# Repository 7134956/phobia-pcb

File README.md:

This repository contains schematic and printed circuit board design files.
There is KiCad project. Refer to the PMC repository for details.

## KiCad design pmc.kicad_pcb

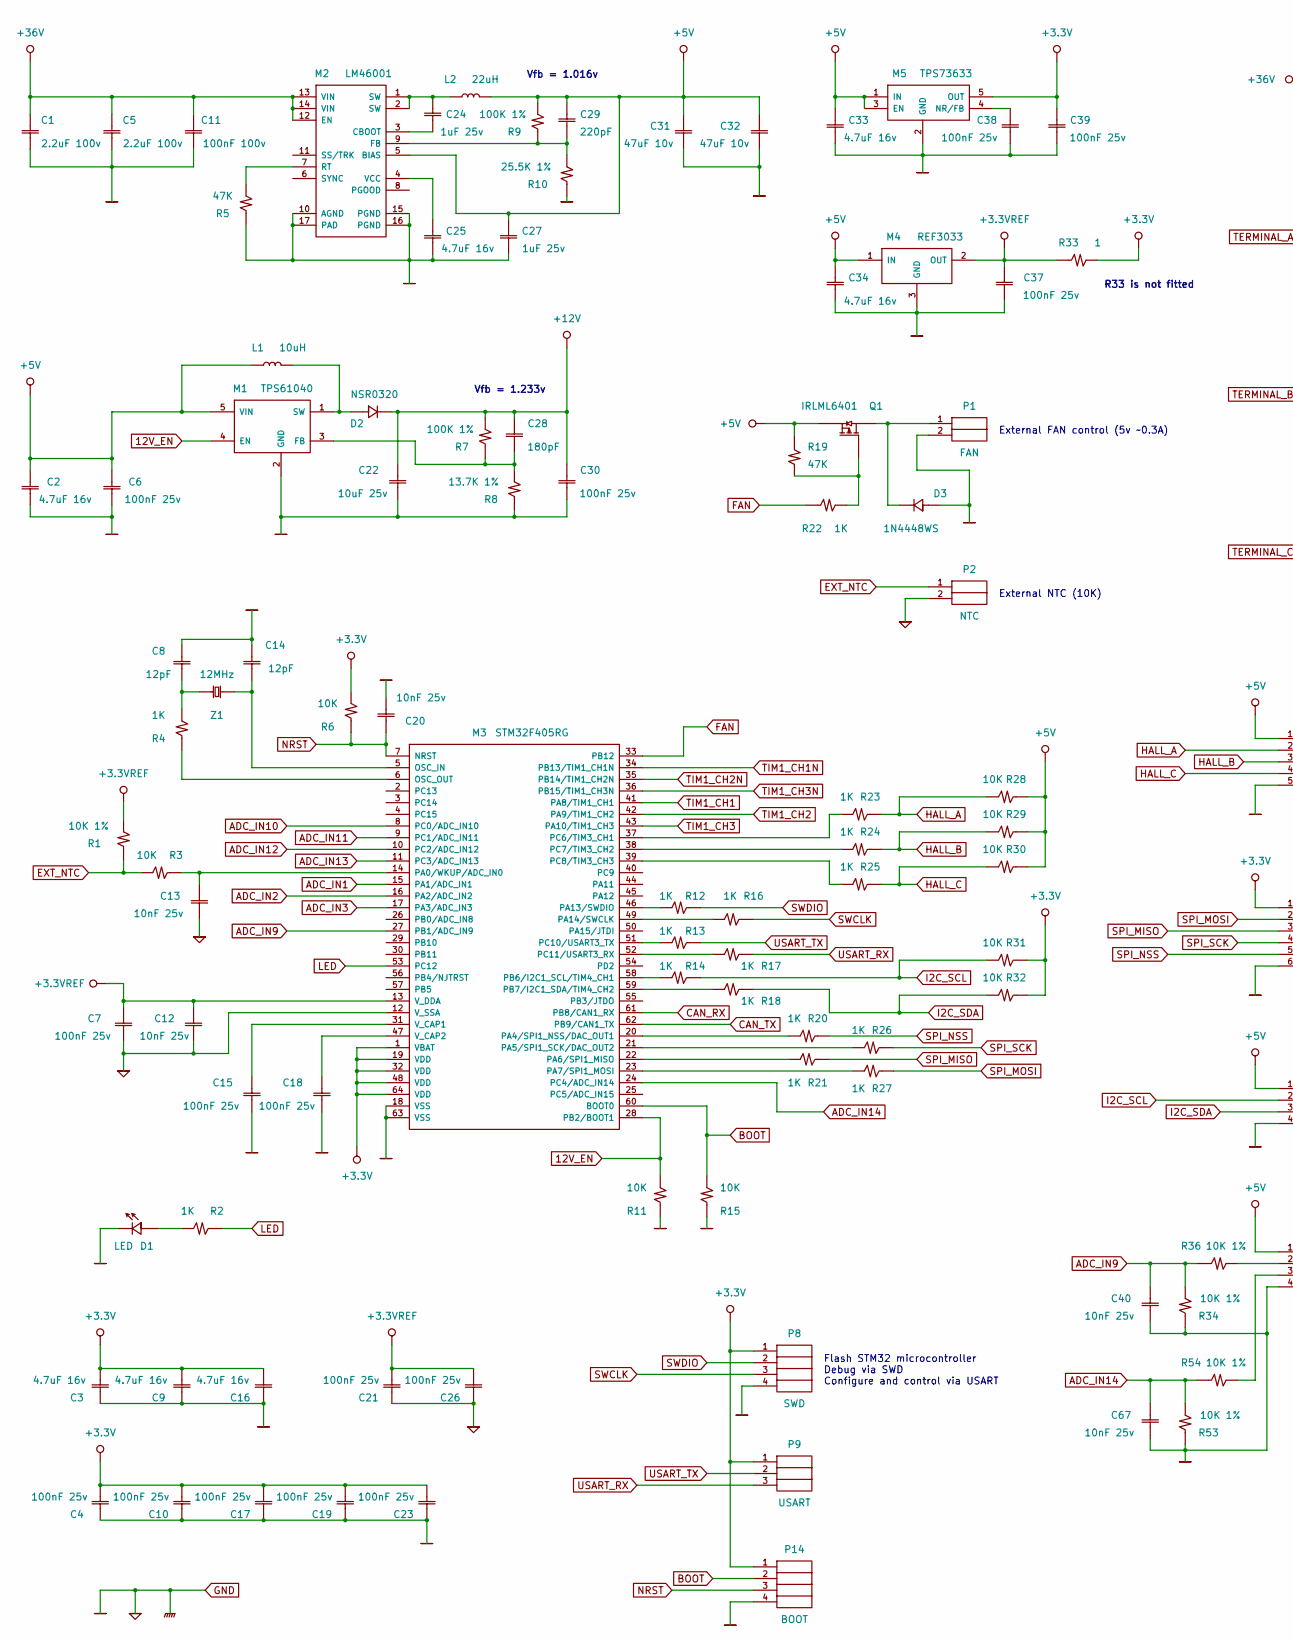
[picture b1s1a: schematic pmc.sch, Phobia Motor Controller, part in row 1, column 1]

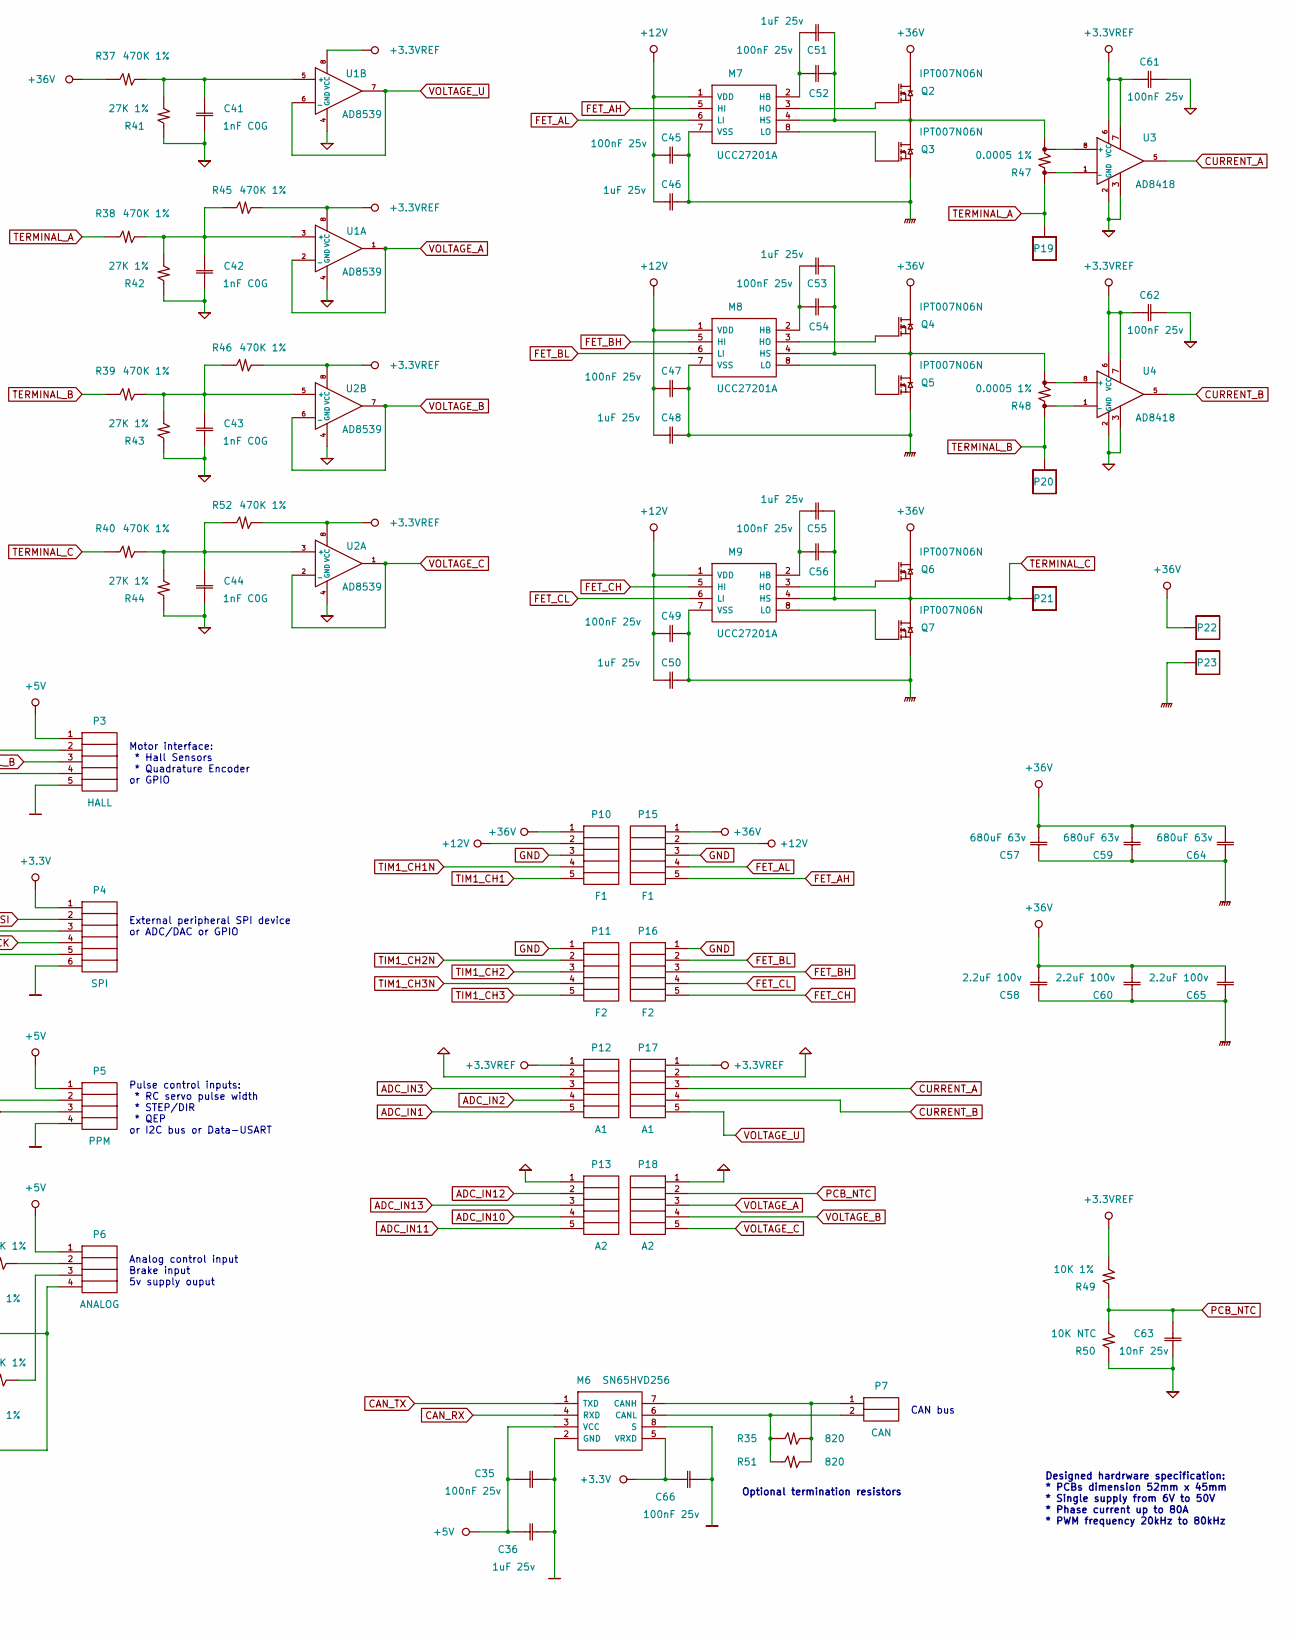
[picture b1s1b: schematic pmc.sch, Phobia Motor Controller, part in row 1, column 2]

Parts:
C1, C5, C58, C60, C65: 2.2uF 100v; SM-1210
C2, C3, C9, C16, C25, C33, C34: 4.7uF 16v; SM-0805
C4, C6, C7, C10, C15, C17, C18, C19, C21, C23, C26, C30, C35, C37, C38, C39, C45, C47, C49, C52, C54, C56, C61, C62, C66: 100nF 25v; SM-0603
C8, C14: 12pF; SM-0603
C11: 100nF 100v; SM-0805
C12, C13, C20, C40, C63, C67: 10nF 25v; SM-0603
C22: 10uF 25v; SM-1210
C24, C27, C36, C46, C48, C50, C51, C53, C55: 1uF 25v; SM-0805
C28: 180pF; SM-0603
C29: 220pF; SM-0603
C31, C32: 47uF 10v; SM-1210
C41, C42, C43, C44: 1nF C0G; SM-0603
C57, C59, C64: 680uF 63v; CE135-E
D1: LED; SM-0603
D2: NSR0320; SM-0805
D3: 1N4448WS; SM-0805
L1: 10uH; COIL-3
L2: 22uH; COIL-8
M1: TPS61040; SOT-23-5
M2: LM46001; HTSSOP-16
M3: STM32F405RG; LQFP-64
M4: REF3033; SOT-23
M5: TPS73633; SOT-23-5
M6: SN65HVD256; SO-8
M7, M8, M9: UCC27201A; SON-8
P1: FAN; PLS-2
P2: NTC; PLS-2
P3: HALL; PLS-5
P4: SPI; PLS-6
P5: PPM; PLS-4
P6: ANALOG; PLS-4
P7: CAN; PLS-2
P8: SWD; PLS-4
P9: USART; PLS-3
P10, P15: F1; PLS-5
P11, P16: F2; PLS-5
P12, P17: A1; PLS-5
P13, P18: A2; PLS-5
P14: BOOT; PLS-4
P19, P20, P21, P22, P23: CONN4; PAD-1
Q1: IRLML6401; SOT-23
Q2, Q3, Q4, Q5, Q6, Q7: IPT007N06N; PG-HSOF-8
R1, R34, R36, R49, R53, R54: 10K 1%; SM-0603
R2, R4, R12, R13, R14, R16, R17, R18, R20, R21, R22, R23, R24, R25, R26, R27: 1K; SM-0603
R3, R6, R11, R15, R28, R29, R30, R31, R32: 10K; SM-0603
R5, R19: 47K; SM-0603
R7, R9: 100K 1%; SM-0603
R8: 13.7K 1%; SM-0603
R10: 25.5K 1%; SM-0603
R33: 1; SM-0603
R35, R51: 820; SM-1206
R37, R38, R39, R40, R45, R46, R52: 470K 1%; SM-0603
R41, R42, R43, R44: 27K 1%; SM-0603
R47, R48: 0.0005 1%; LR2512-4
R50: 10K NTC; SM-0805
U1, U2: AD8539; MSOP-8
U3, U4: AD8418; MSOP-8
Z1: 12MHz; SM-Z3225

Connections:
12V_EN: M1.4 (EN), M3.28 (PB2/BOOT1), R11.2
+3.3V: C3.1, C4.1, C9.1, C10.1, C16.1, C17.1, C19.1, C23.1, C39.1, C66.1, M3.1 (VBAT), M3.19 (VDD), M3.32 (VDD), M3.48 (VDD), M3.64 (VDD), M5.5 (OUT), M6.5 (VRXD), P4.1, P8.1, P9.1, P14.1, R6.2, R31.1, R32.1, R33.2
+3.3VREF: C7.1, C12.1, C21.1, C26.1, C37.1, C61.2, C62.2, M3.13 (V_DDA), M4.2 (OUT), P12.1, P17.1, R1.2, R33.1, R45.2, R46.2, R49.2, R52.2, U1.8 (VCC), U2.8 (VCC), U3.6 (VCC), U3.7, U4.6 (VCC), U4.7
+5V: C2.1, C6.1, C27.1, C29.1, C31.1, C32.1, C33.1, C34.1, C35.2, C36.2, L1.1, L2.2, M1.5 (VIN), M2.5 (BIAS), M4.1 (IN), M5.1 (IN), M5.3 (EN), M6.3 (VCC), P3.1, P5.1, P6.1, Q1.2 (S), R9.2, R19.1, R28.1, R29.1, R30.1
+12V: C22.1, C28.1, C30.1, C45.2, C46.1, C47.2, C48.2, C49.2, C50.2, D2.1, M7.1 (VDD), M8.1 (VDD), M9.1 (VDD), P10.2, P15.2, R7.2
+36V: C1.2, C5.2, C11.2, C57.1, C58.1, C59.1, C60.1, C64.1, C65.1, M2.12 (EN), M2.13 (VIN), M2.14 (VIN), P10.1, P15.1, P22.1, Q2.3 (D), Q4.3 (D), Q6.3 (D), R37.1
ADC_IN1: M3.15 (PA1/ADC_IN1), P12.5
ADC_IN2: M3.16 (PA2/ADC_IN2), P12.4
ADC_IN3: M3.17 (PA3/ADC_IN3), P12.3
ADC_IN9: C40.2, M3.27 (PB1/ADC_IN9), R34.2, R36.1
ADC_IN10: M3.8 (PC0/ADC_IN10), P13.4
ADC_IN11: M3.9 (PC1/ADC_IN11), P13.5
ADC_IN12: M3.10 (PC2/ADC_IN12), P13.2
ADC_IN13: M3.11 (PC3/ADC_IN13), P13.3
ADC_IN14: C67.2, M3.24 (PC4/ADC_IN14), R53.2, R54.1
BOOT: M3.60 (BOOT0), P14.2, R15.2
CAN_RX: M3.61 (PB8/CAN1_RX), M6.4 (RXD)
CAN_TX: M3.62 (PB9/CAN1_TX), M6.1 (TXD)
CURRENT_A: P17.3, U3.5
CURRENT_B: P17.4, U4.5
EXT_NTC: P2.1, R1.1, R3.2
FAN: M3.33 (PB12), R22.1
FET_AH: M7.5 (HI), P15.5
FET_AL: M7.6 (LI), P15.4
FET_BH: M8.5 (HI), P16.3
FET_BL: M8.6 (LI), P16.2
FET_CH: M9.5 (HI), P16.5
FET_CL: M9.6 (LI), P16.4
GND: C1.1, C2.2, C3.2, C4.2, C5.1, C6.2, C7.2, C8.1, C9.2, C10.2, C11.1, C12.2, C13.1, C14.1, C15.2, C16.2, C17.2, C18.2, C19.2, C20.1, C21.2, C22.2, C23.2, C25.2, C26.2, C27.2, C30.2, C31.2, C32.2, C33.2, C34.2, C35.1, C36.1, C37.2, C38.2, C39.2, C40.1, C41.2, C42.2, C43.2, C44.2, C45.1, C46.2, C47.1, C48.1, C49.1, C50.1, C57.2, C58.2, C59.2, C60.2, C61.1, C62.1, C63.1, C64.2, C65.2, C66.2, C67.1, D1.1, D3.2, M1.2 (GND), M2.10 (AGND), M2.15 (PGND), M2.16 (PGND), M2.17 (PAD), M3.12 (V_SSA), M3.18 (VSS), M3.63 (VSS), M4.3 (GND), M5.2 (GND), M6.2 (GND), M6.8 (S), M7.7 (VSS), M8.7 (VSS), M9.7 (VSS), P1.2, P2.2, P3.5, P4.6, P5.4, P6.4, P8.4, P10.3, P11.1, P12.2, P13.1, P14.4, P15.3, P16.1, P17.2, P18.1, P23.1, Q3.2 (S), Q5.2 (S), Q7.2 (S), R5.1, R8.1, R10.1, R11.1, R15.1, R34.1, R41.1, R42.1, R43.1, R44.1, R50.1, R53.1, U1.4 (GND), U2.4 (GND), U3.2 (GND), U3.3, U4.2 (GND), U4.3; also elsewhere on the board
HALL_A: P3.2, R23.1, R28.2
HALL_B: P3.3, R24.1, R29.2
HALL_C: P3.4, R25.1, R30.2
I2C_SCL: P5.2, R14.1, R31.2
I2C_SDA: P5.3, R18.1, R32.2
LED: M3.53 (PC12), R2.1
NC: U3.4 (NC), U4.4 (NC)
NRST: C20.2, M3.7 (NRST), P14.3, R6.1
unnamed: C8.2, R4.2, Z1.1
unnamed: C13.2, M3.14 (PA0/WKUP/ADC_IN0), R3.1
unnamed: C14.2, M3.5 (OSC_IN), Z1.2
unnamed: C15.1, M3.31 (V_CAP1)
unnamed: C18.1, M3.47 (V_CAP2)
unnamed: C24.1, L2.1, M2.1 (SW), M2.2 (SW)
unnamed: C24.2, M2.3 (CBOOT)
unnamed: C25.1, M2.4 (VCC)
unnamed: C28.2, M1.3 (FB), R7.1, R8.2
unnamed: C29.2, M2.9 (FB), R9.1, R10.2
unnamed: C38.1, M5.4 (NR/FB)
unnamed: C41.1, R37.2, R41.2, U1.5 (+)
unnamed: C42.1, R38.2, R42.2, R45.1, U1.3 (+)
unnamed: C43.1, R39.2, R43.2, R46.1, U2.5 (+)
unnamed: C44.1, R40.2, R44.2, R52.1, U2.3 (+)
unnamed: C51.1, C52.1, M7.4 (HS), Q2.2 (S), Q3.3 (D), R47.1
unnamed: C51.2, C52.2, M7.2 (HB)
unnamed: C53.1, C54.1, M8.4 (HS), Q4.2 (S), Q5.3 (D), R48.1
unnamed: C53.2, C54.2, M8.2 (HB)
unnamed: C55.2, C56.2, M9.2 (HB)
unnamed: D1.2, R2.2
unnamed: D2.2, L1.2, M1.1 (SW)
unnamed: D3.1, P1.1, Q1.3 (D)
unnamed: M2.7 (RT), R5.2
unnamed: M3.6 (OSC_OUT), R4.1
unnamed: M3.20 (PA4/SPI1_NSS/DAC_OUT1), R20.2
unnamed: M3.21 (PA5/SPI1_SCK/DAC_OUT2), R26.2
unnamed: M3.22 (PA6/SPI1_MISO), R21.2
unnamed: M3.23 (PA7/SPI1_MOSI), R27.2
unnamed: M3.37 (PC6/TIM3_CH1), R23.2
unnamed: M3.38 (PC7/TIM3_CH2), R24.2
unnamed: M3.39 (PC8/TIM3_CH3), R25.2
unnamed: M3.46 (PA13/SWDIO), R12.2
unnamed: M3.49 (PA14/SWCLK), R16.2
unnamed: M3.51 (PC10/USART3_TX), R13.2
unnamed: M3.52 (PC11/USART3_RX), R17.2
unnamed: M3.58 (PB6/I2C1_SCL/TIM4_CH1), R14.2
unnamed: M3.59 (PB7/I2C1_SDA/TIM4_CH2), R18.2
unnamed: M6.6 (CANL), P7.2, R35.1, R51.1
unnamed: M6.7 (CANH), P7.1, R35.2, R51.2
unnamed: M7.3 (HO), Q2.1 (G)
unnamed: M7.8 (LO), Q3.1 (G)
unnamed: M8.3 (HO), Q4.1 (G)
unnamed: M8.8 (LO), Q5.1 (G)
unnamed: M9.3 (HO), Q6.1 (G)
unnamed: M9.8 (LO), Q7.1 (G)
unnamed: P6.2, R36.2
unnamed: P6.3, R54.2
unnamed: Q1.1 (G), R19.2, R22.2
unnamed: R47.3, U3.8 (+)
unnamed: R47.4, U3.1 (_)
unnamed: R48.3, U4.8 (+)
unnamed: R48.4, U4.1 (_)
PCB_NTC: C63.2, P18.2, R49.1, R50.2
SPI_MISO: P4.3, R21.1
SPI_MOSI: P4.2, R27.1
SPI_NSS: P4.5, R20.1
SPI_SCK: P4.4, R26.1
SWCLK: P8.3, R16.1
SWDIO: P8.2, R12.1
TERMINAL_A: P19.1, R38.1, R47.2
TERMINAL_B: P20.1, R39.1, R48.2
TERMINAL_C: C55.1, C56.1, M9.4 (HS), P21.1, Q6.2 (S), Q7.3 (D), R40.1
TIM1_CH1: M3.41 (PA8/TIM1_CH1), P10.5
TIM1_CH1N: M3.34 (PB13/TIM1_CH1N), P10.4
TIM1_CH2: M3.42 (PA9/TIM1_CH2), P11.3
TIM1_CH2N: M3.35 (PB14/TIM1_CH2N), P11.2
TIM1_CH3: M3.43 (PA10/TIM1_CH3), P11.5
TIM1_CH3N: M3.36 (PB15/TIM1_CH3N), P11.4
USART_RX: P9.3, R17.1
USART_TX: P9.2, R13.1
VOLTAGE_A: P18.3, U1.1, U1.2 (_)
VOLTAGE_B: P18.4, U2.6 (_), U2.7
VOLTAGE_C: P18.5, U2.1, U2.2 (_)
VOLTAGE_U: P17.5, U1.6 (_), U1.7

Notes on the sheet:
Motor interface: * Hall Sensors * Quadrature Encoder or GPIO
External peripheral SPI device or ADC/DAC or GPIO
Pulse control inputs: * RC servo pulse width * STEP/DIR * QEP or I2C bus or Data-USART
Flash STM32 microcontroller Debug via SWD Configure and control via USART
Designed hardrware specification: * PCBs dimension 52mm x 45mm * Single supply from 6V to 50V * Phase current up to 80A * PWM frequency 20kHz to 80kHz
Optional termination resistors
Analog control input Brake input 5v supply ouput
External NTC (10K)
External FAN control (5v ~~0.3A)
CAN bus
R33 is not fitted
Vfb = 1.016v
Vfb = 1.233v

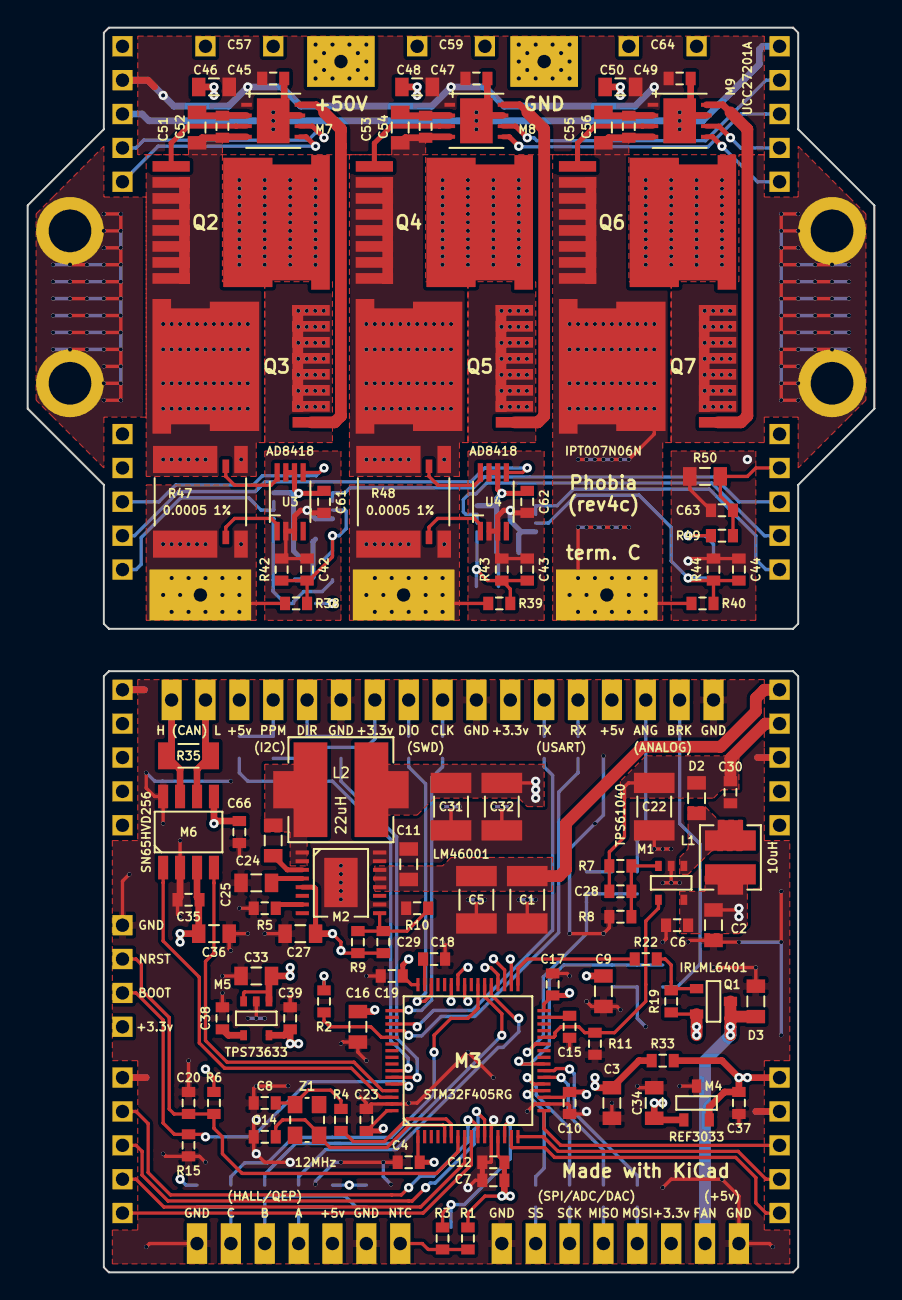
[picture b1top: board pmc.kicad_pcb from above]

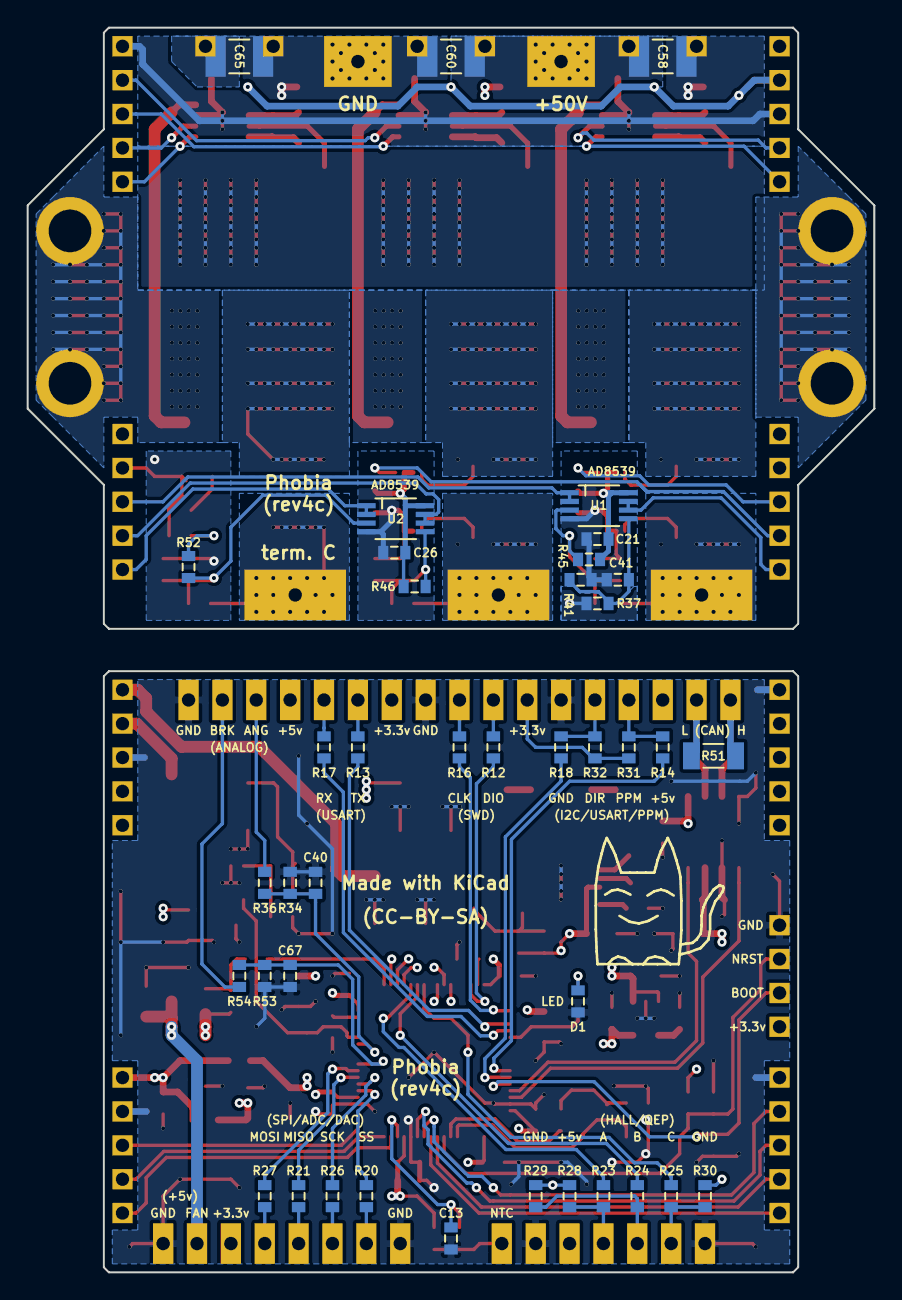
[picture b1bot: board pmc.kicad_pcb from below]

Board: 8 copper layers, 63.5 x 93.3 mm, 174 parts (40 on the bottom side), 112 nets.

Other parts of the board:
PLS-1, PLS-1#2, PLS-1#3, PLS-1#4: VAL**; PLS-1

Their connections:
GND: PLS-1.1, PLS-1#2.1, PLS-1#3.1, PLS-1#4.1; also elsewhere on the board

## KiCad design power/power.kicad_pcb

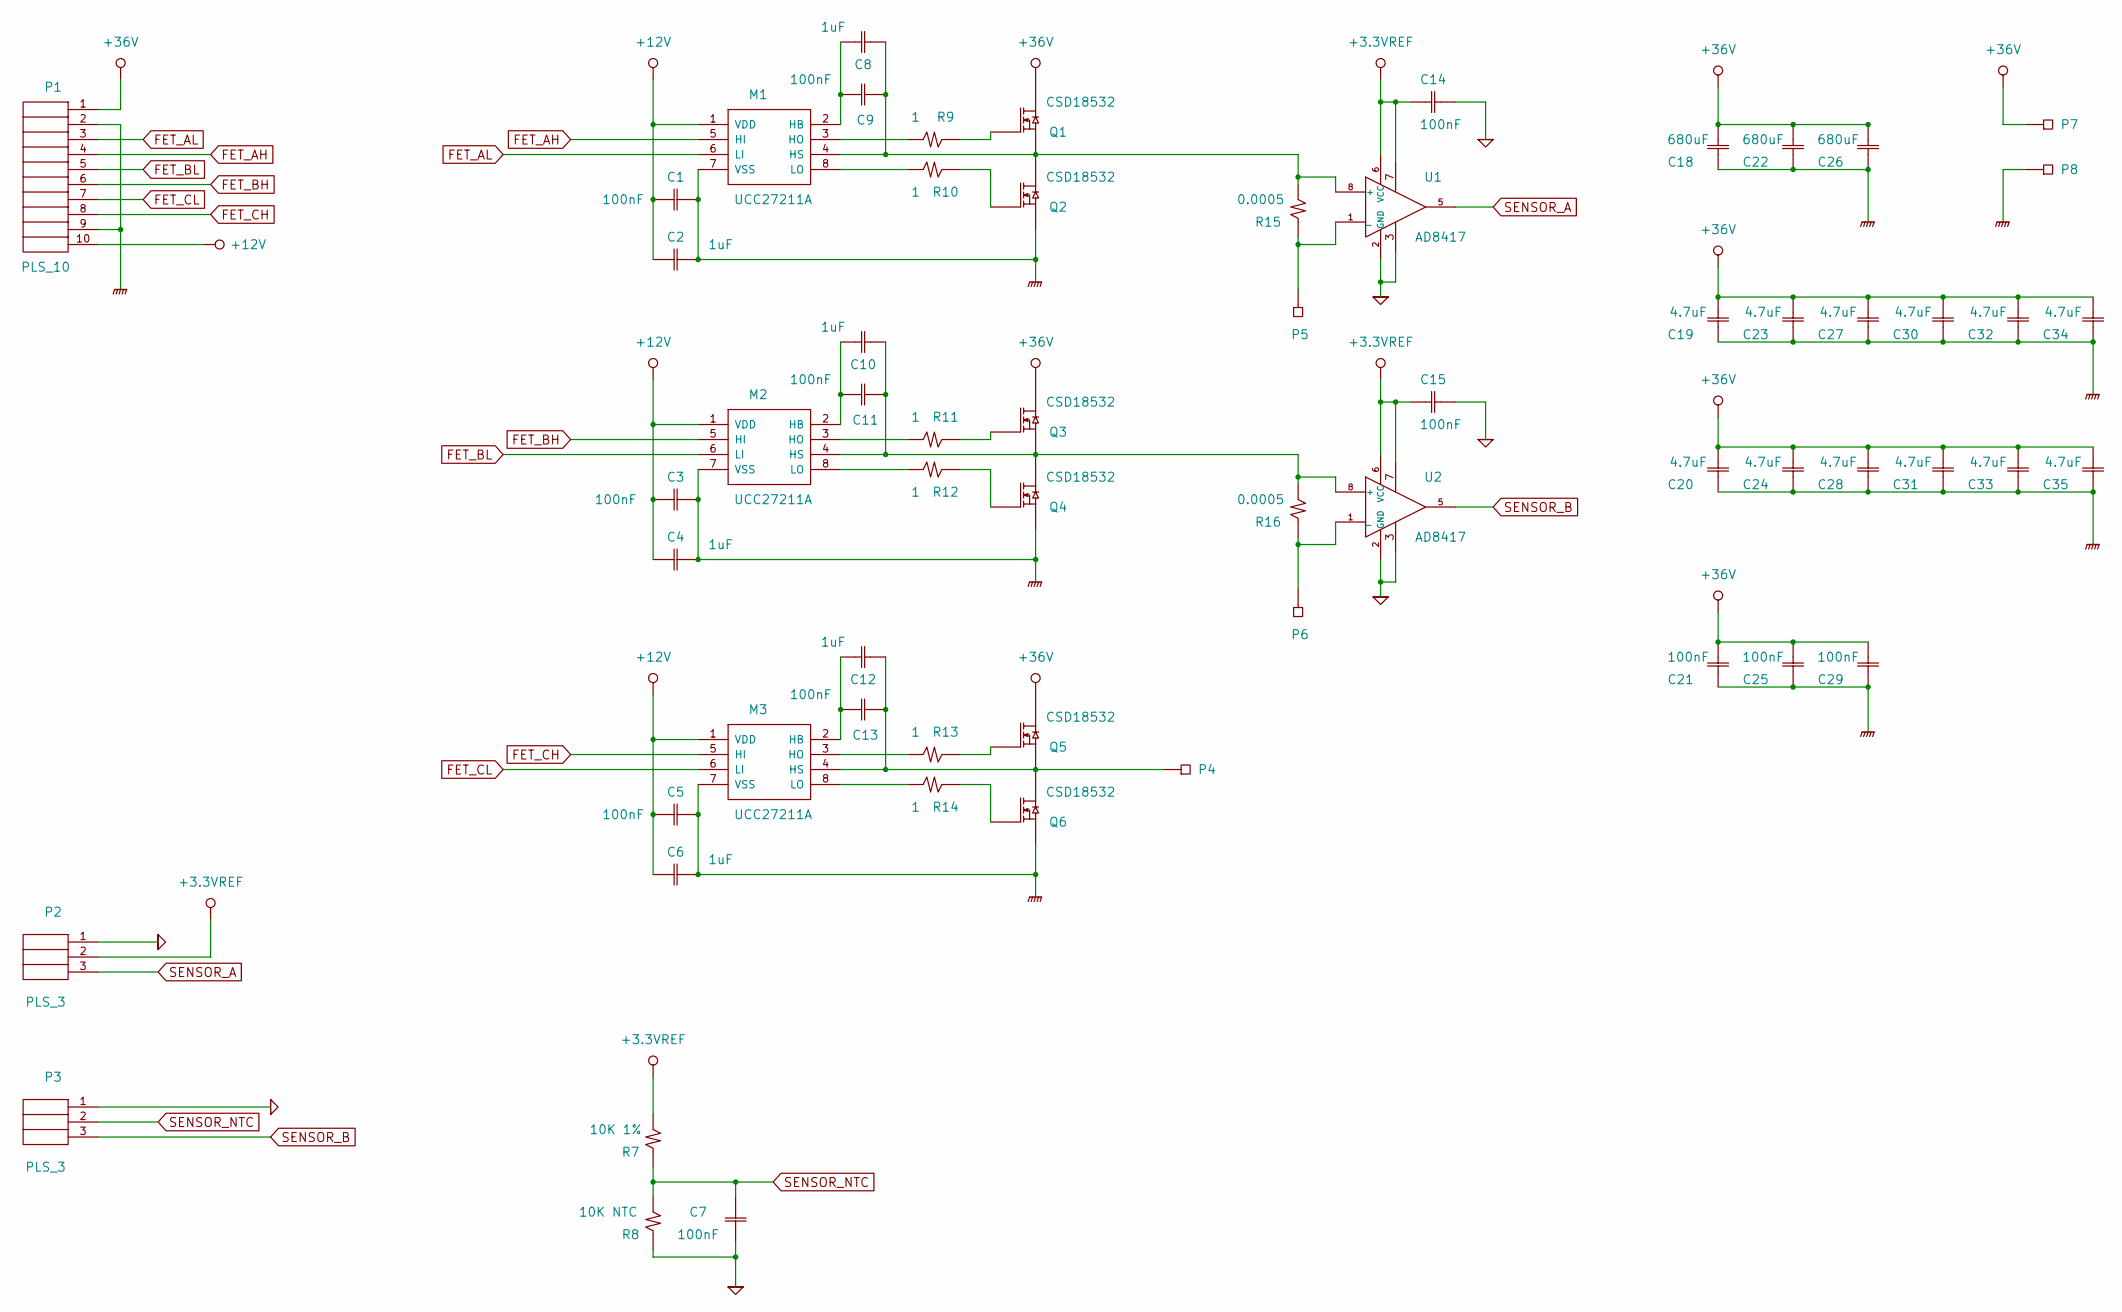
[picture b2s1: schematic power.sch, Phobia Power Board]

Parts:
C1, C3, C5, C7, C9, C11, C13, C14, C15: 100nF; SM0603
C2, C4, C6, C8, C10, C12: 1uF; SM0805
C18: 680uF; CE135L; Part Number EEU-FR1J681L
C19, C20, C23, C24, C27, C28, C30, C31, C32, C33, C34, C35: 4.7uF; SM2220
C21, C25, C29: 100nF; SM0805
C22, C26: 680uF; CE135L
M1, M2, M3: UCC27211A; SON8
P1: PLS_10; PLS10
P2, P3: PLS_3; PLS3
P4: C; PAD2
P5: A; PAD2
P6: B; PAD2
P7: VDD; PAD2
P8: GND; PAD2
Q1, Q2, Q3, Q4, Q5, Q6: CSD18532; VSON56
R7: 10K 1%; SM0603
R8: 10K NTC; SM0805
R9, R10, R11, R12, R13, R14: 1; SM0603
R15, R16: 0.0005; LR2512
U1, U2: AD8417; MSOP8

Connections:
+3.3V: C14.2, C15.2, P2.2, R7.2, U1.6 (VCC), U1.7, U2.6 (VCC), U2.7
+12V: C1.2, C2.1, C3.2, C4.2, C5.2, C6.2, M1.1 (VDD), M2.1 (VDD), M3.1 (VDD), P1.10
+36V: C18.1, C19.1, C20.1, C21.1, C22.1, C23.1, C24.1, C25.1, C26.1, C27.1, C28.1, C29.1, C30.1, C31.1, C32.1, C33.1, C34.1, C35.1, P1.1, P7.1, Q1.5 (D), Q1.6 (D), Q1.7 (D), Q1.8 (D), Q3.5 (D), Q3.6 (D), Q3.7 (D), Q3.8 (D), Q5.5 (D), Q5.6 (D), Q5.7 (D), Q5.8 (D)
AGND: C7.1, C14.1, C15.1, P2.1, P3.1, R8.1, U1.2 (GND), U1.3, U2.2 (GND), U2.3
FET_AH: M1.5 (HI), P1.4
FET_AL: M1.6 (LI), P1.3
FET_BH: M2.5 (HI), P1.6
FET_BL: M2.6 (LI), P1.5
FET_CH: M3.5 (HI), P1.8
FET_CL: M3.6 (LI), P1.7
NC: U1.4 (NC), U2.4 (NC)
unnamed: C8.1, C9.1, M1.4 (HS), Q1.1 (S), Q1.2 (S), Q1.3 (S), Q2.5 (D), Q2.6 (D), Q2.7 (D), Q2.8 (D), R15.2, U1.8 (+)
unnamed: C8.2, C9.2, M1.2 (HB)
unnamed: C10.1, C11.1, M2.4 (HS), Q3.1 (S), Q3.2 (S), Q3.3 (S), Q4.5 (D), Q4.6 (D), Q4.7 (D), Q4.8 (D), R16.2, U2.8 (+)
unnamed: C10.2, C11.2, M2.2 (HB)
unnamed: C12.1, C13.1, M3.4 (HS), P4.1, Q5.1 (S), Q5.2 (S), Q5.3 (S), Q6.5 (D), Q6.6 (D), Q6.7 (D), Q6.8 (D)
unnamed: C12.2, C13.2, M3.2 (HB)
unnamed: M1.3 (HO), R9.2
unnamed: M1.8 (LO), R10.2
unnamed: M2.3 (HO), R11.2
unnamed: M2.8 (LO), R12.2
unnamed: M3.3 (HO), R13.2
unnamed: M3.8 (LO), R14.2
unnamed: P5.1, R15.1, U1.1 (_)
unnamed: P6.1, R16.1, U2.1 (_)
unnamed: Q1.4 (G), R9.1
unnamed: Q2.4 (G), R10.1
unnamed: Q3.4 (G), R11.1
unnamed: Q4.4 (G), R12.1
unnamed: Q5.4 (G), R13.1
unnamed: Q6.4 (G), R14.1
PGND: C1.1, C2.2, C3.1, C4.1, C5.1, C6.1, C18.2, C19.2, C20.2, C21.2, C22.2, C23.2, C24.2, C25.2, C26.2, C27.2, C28.2, C29.2, C30.2, C31.2, C32.2, C33.2, C34.2, C35.2, M1.7 (VSS), M2.7 (VSS), M3.7 (VSS), P1.2, P1.9, P8.1, Q2.1 (S), Q2.2 (S), Q2.3 (S), Q4.1 (S), Q4.2 (S), Q4.3 (S), Q6.1 (S), Q6.2 (S), Q6.3 (S)
SENSOR_A: P2.3, U1.5
SENSOR_B: P3.3, U2.5
SENSOR_NTC: C7.2, P3.2, R7.1, R8.2

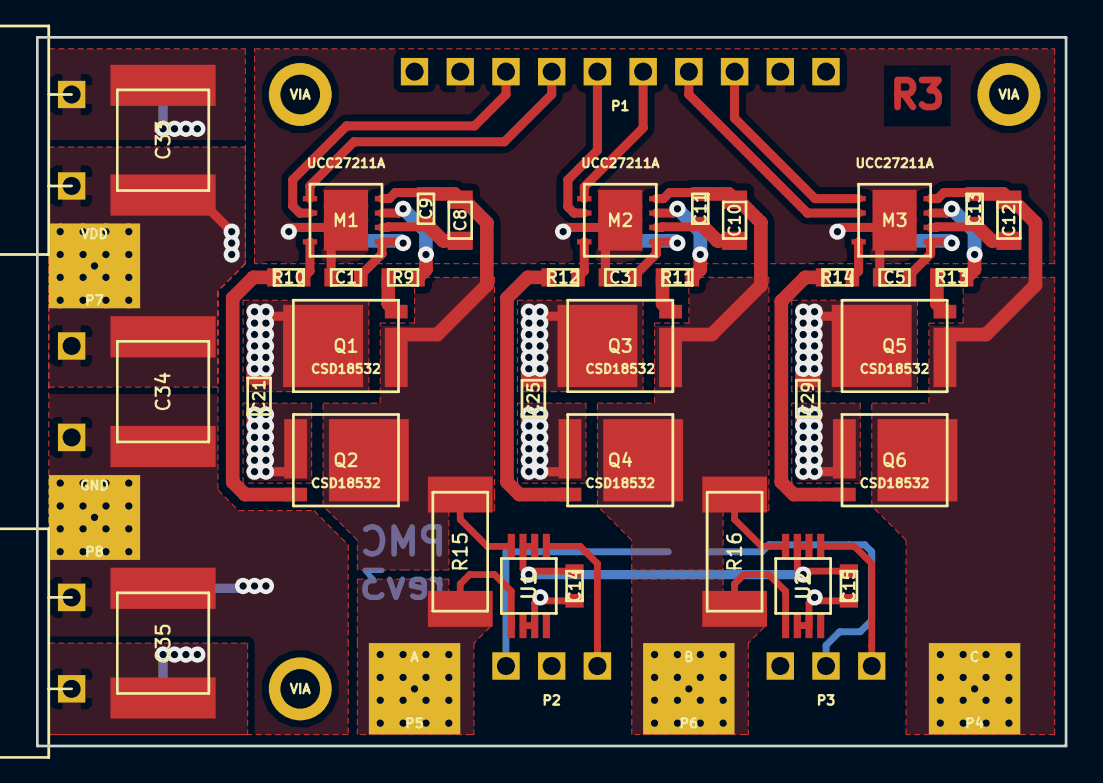
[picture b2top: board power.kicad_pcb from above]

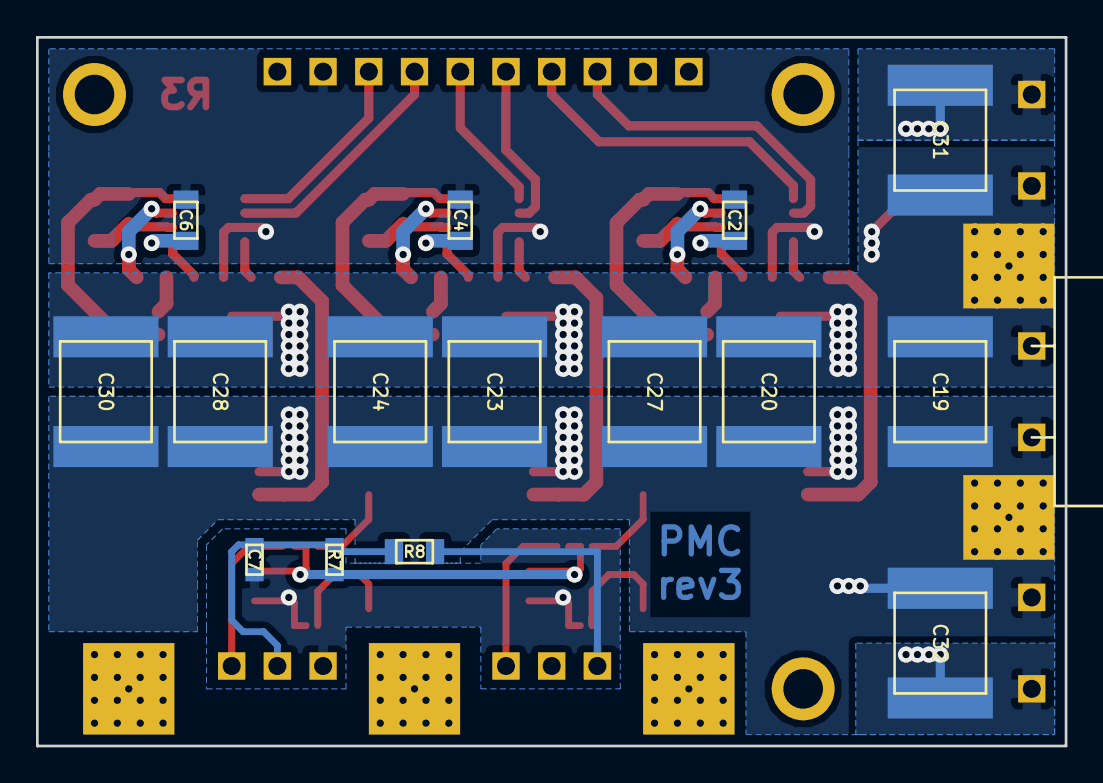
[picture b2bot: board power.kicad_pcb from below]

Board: 4 copper layers, 57.2 x 39.4 mm, 65 parts (16 on the bottom side), 35 nets.

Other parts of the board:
VIA: PLS1
VIA#2, VIA#3: PLS1

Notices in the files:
pmc.kicad_pcb:
(CC-BY-SA)
